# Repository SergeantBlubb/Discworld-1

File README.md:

# Discworld-1
First rep for my Stuff

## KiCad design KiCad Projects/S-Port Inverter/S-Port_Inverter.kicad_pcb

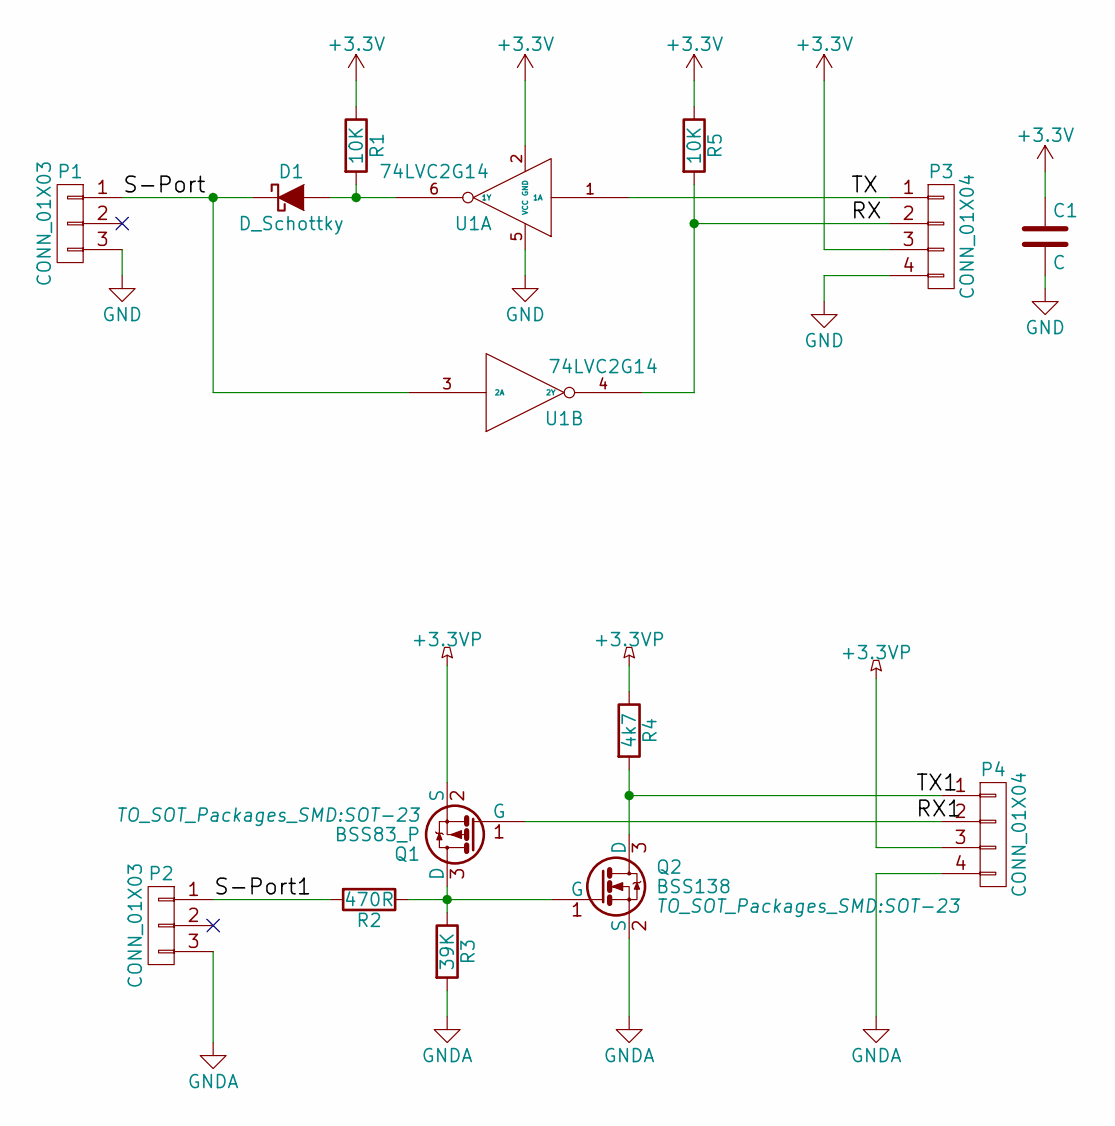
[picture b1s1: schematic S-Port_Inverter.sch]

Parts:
C1: C; C_0402
D1: D_Schottky; SOD-323
P1, P2: CONN_01X03; Pin_Header_Angled_1x03
P3, P4: CONN_01X04; Pin_Header_Angled_1x04
Q1: BSS83_P; SOT-23
Q2: BSS138; SOT-23
R1, R5: 10K; R_0402
R2: 470R; R_0402
R3: 39K; R_0402
R4: 4k7; R_0402
U1: 74LVC2G14; SOT-23-6

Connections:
+3.3VP: P4.3, Q1.2 (S), R4.1
+3V3: C1.1, P3.3, R1.1, R5.1, U1.2 (GND)
/RX: P3.2, R5.2, U1.4 (2Y)
/RX1: P4.2, Q1.1 (G)
/S-Port: D1.1 (K), P1.1, U1.3 (2A)
/S-Port1: P2.1, R2.2
/TX: P3.1, U1.1 (1A)
/TX1: P4.1, Q2.3 (D), R4.2
GND: C1.2, P1.3, P3.4, U1.5 (VCC)
GNDA: P2.3, P4.4, Q2.2 (S), R3.2
unnamed: D1.2 (A), R1.2, U1.6 (1Y)
unnamed: Q1.3 (D), Q2.1 (G), R2.1, R3.1

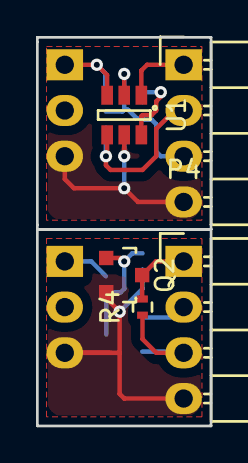
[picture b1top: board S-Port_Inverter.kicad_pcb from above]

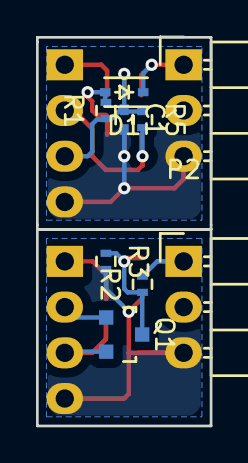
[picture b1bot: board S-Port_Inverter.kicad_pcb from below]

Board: 2 copper layers, 9.7 x 21.6 mm, 14 parts (9 on the bottom side), 12 nets.

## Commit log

2015-02-06 Initial release
2015-09-21 Inital Folder Upload
2015-09-21 Inital Flight Control V1 Upload
2016-01-15 Initial_S-Port Inverter Design
2016-01-15 Initial Lib
2016-01-15 Initial GPS-Module
2016-01-15 Inital Buffer
2016-01-15 Initial FC
2016-01-15 Delete
